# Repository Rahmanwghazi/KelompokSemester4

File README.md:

# Kelompok Mata Kuliah 
Interface, Peripheral, & Komunikasi, Sistem Mikrokontroller dan Sistem Kendali

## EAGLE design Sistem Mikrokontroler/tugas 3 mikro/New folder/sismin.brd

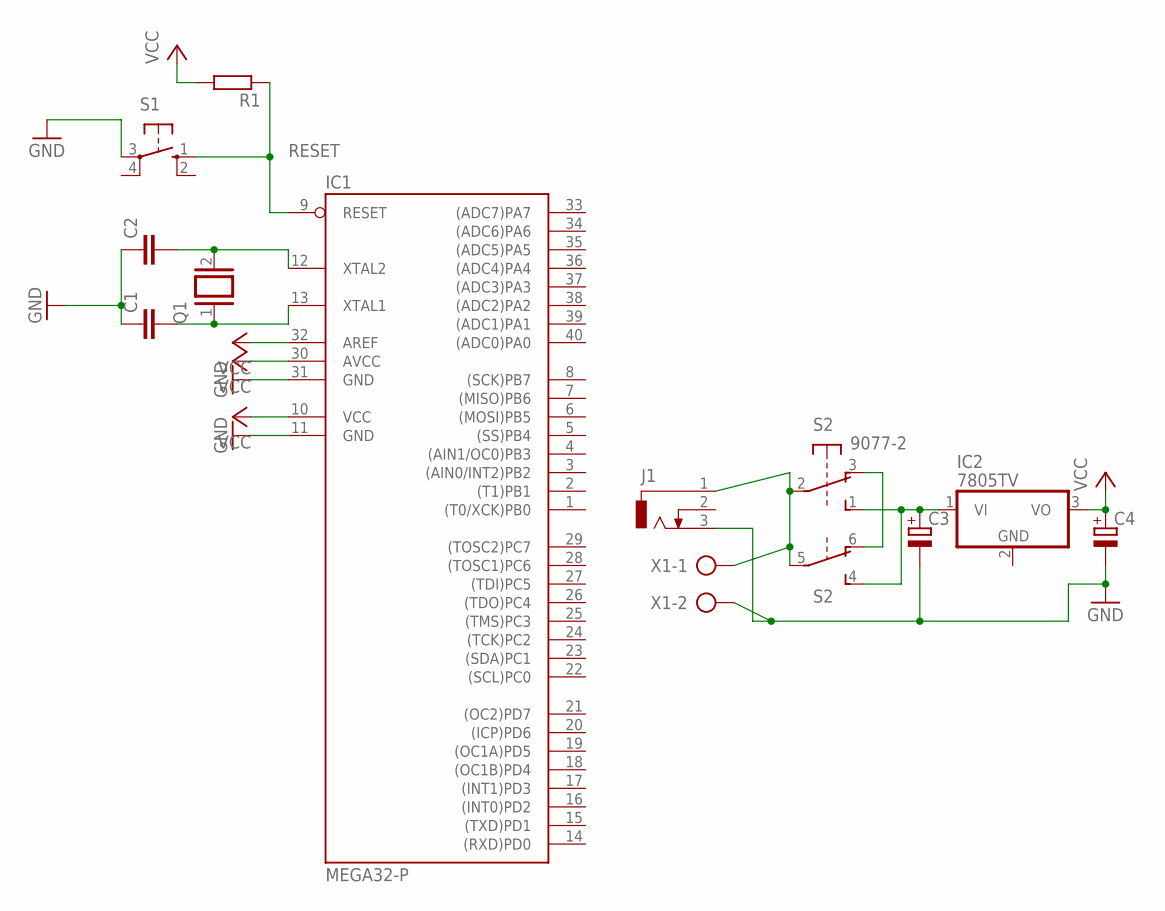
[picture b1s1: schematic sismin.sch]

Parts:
C1, C2: C-EU025-025X050; C025-025X050
C3, C4: CPOL-EUE2.5-5; E2,5-5
IC1: MEGA32-P; DIL40
IC2: 7805TV; TO220V
J1: DCJ0303
Q1: XTAL/S; QS
R1: R-EU_0204/7; 0204/7
S1: 10-XX; B3F-10XX
S2: 9077-2
X1: AK300/2

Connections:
GND: C1.1, C2.1, C3.-, C4.-, IC1.11 (GND), IC1.31 (GND), J1.3, S1.3, X1.2
unnamed: J1.1, S2.2, S2.5, X1.1
unnamed: C2.2, IC1.12 (XTAL2), Q1.2
unnamed: C1.2, IC1.13 (XTAL1), Q1.1
unnamed: S2.3 (O), S2.6 (O)
unnamed: C3.+, IC2.1 (VI), S2.1 (S), S2.4 (S)
RESET: IC1.9 (RESET), R1.1, S1.1 (S)
VCC: C4.+, IC1.10 (VCC), IC1.30 (AVCC), IC1.32 (AREF), IC2.3 (VO), R1.2

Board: 2 copper layers, 12 parts (0 on the bottom side), 8 nets, no tracks yet.

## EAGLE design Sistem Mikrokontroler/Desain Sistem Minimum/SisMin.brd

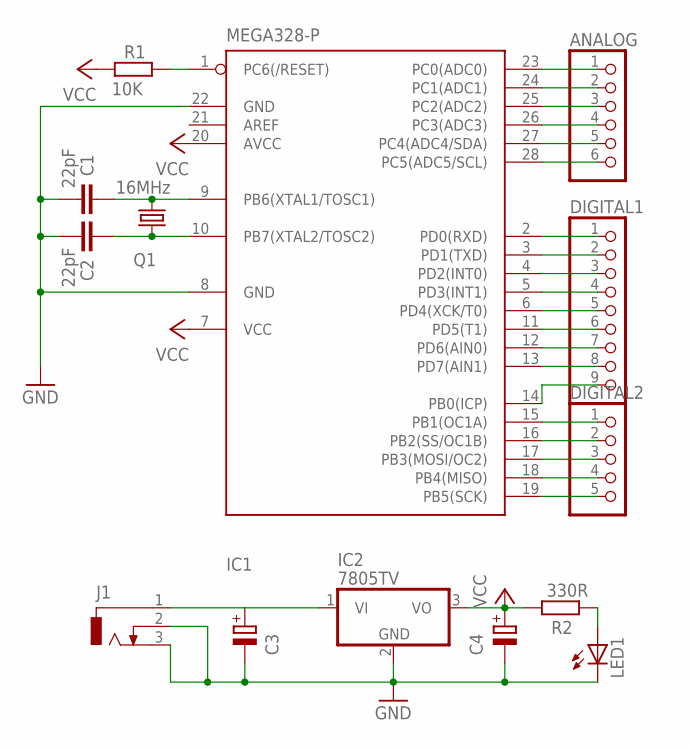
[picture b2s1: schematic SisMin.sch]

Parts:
ANALOG: PINHD-1X6; 1X06
C1, C2: 22pF; C025-024X044
C3, C4: CPOL-EUE2.5-6; E2,5-6
DIGITAL1: PINHD-1X9; 1X09
DIGITAL2: PINHD-1X5; 1X05
IC1: MEGA328-P; DIL28-3
IC2: 7805TV; TO220V
J1: DCJ0303
LED1: LED3MM
Q1: 16MHz; HC49U70
R1: 10K; 0207/10
R2: 330R; 0207/10

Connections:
GND: C1.2, C2.2, C3.-, C4.-, IC1.8 (GND), IC1.22 (GND), IC2.2 (GND), J1.2, J1.3, LED1.K (C)
unnamed: IC1.1 (PC6(/RESET)), R1.2
unnamed: C1.1, IC1.9 (PB6(XTAL1/TOSC1)), Q1.1
unnamed: C2.1, IC1.10 (PB7(XTAL2/TOSC2)), Q1.2
unnamed: ANALOG.1, IC1.23 (PC0(ADC0))
unnamed: ANALOG.2, IC1.24 (PC1(ADC1))
unnamed: ANALOG.3, IC1.25 (PC2(ADC2))
unnamed: ANALOG.4, IC1.26 (PC3(ADC3))
unnamed: ANALOG.5, IC1.27 (PC4(ADC4/SDA))
unnamed: ANALOG.6, IC1.28 (PC5(ADC5/SCL))
unnamed: DIGITAL1.1, IC1.2 (PD0(RXD))
unnamed: DIGITAL1.2, IC1.3 (PD1(TXD))
unnamed: DIGITAL1.3, IC1.4 (PD2(INT0))
unnamed: DIGITAL1.4, IC1.5 (PD3(INT1))
unnamed: DIGITAL1.5, IC1.6 (PD4(XCK/T0))
unnamed: DIGITAL1.6, IC1.11 (PD5(T1))
unnamed: DIGITAL1.7, IC1.12 (PD6(AIN0))
unnamed: DIGITAL1.8, IC1.13 (PD7(AIN1))
unnamed: DIGITAL1.9, IC1.14 (PB0(ICP))
unnamed: DIGITAL2.1, IC1.15 (PB1(OC1A))
unnamed: DIGITAL2.2, IC1.16 (PB2(SS/OC1B))
unnamed: DIGITAL2.3, IC1.17 (PB3(MOSI/OC2))
unnamed: DIGITAL2.4, IC1.18 (PB4(MISO))
unnamed: DIGITAL2.5, IC1.19 (PB5(SCK))
unnamed: C3.+, IC2.1 (VI), J1.1
unnamed: LED1.A, R2.2
VCC: C4.+, IC1.7 (VCC), IC1.20 (AVCC), IC2.3 (VO), R1.1, R2.1

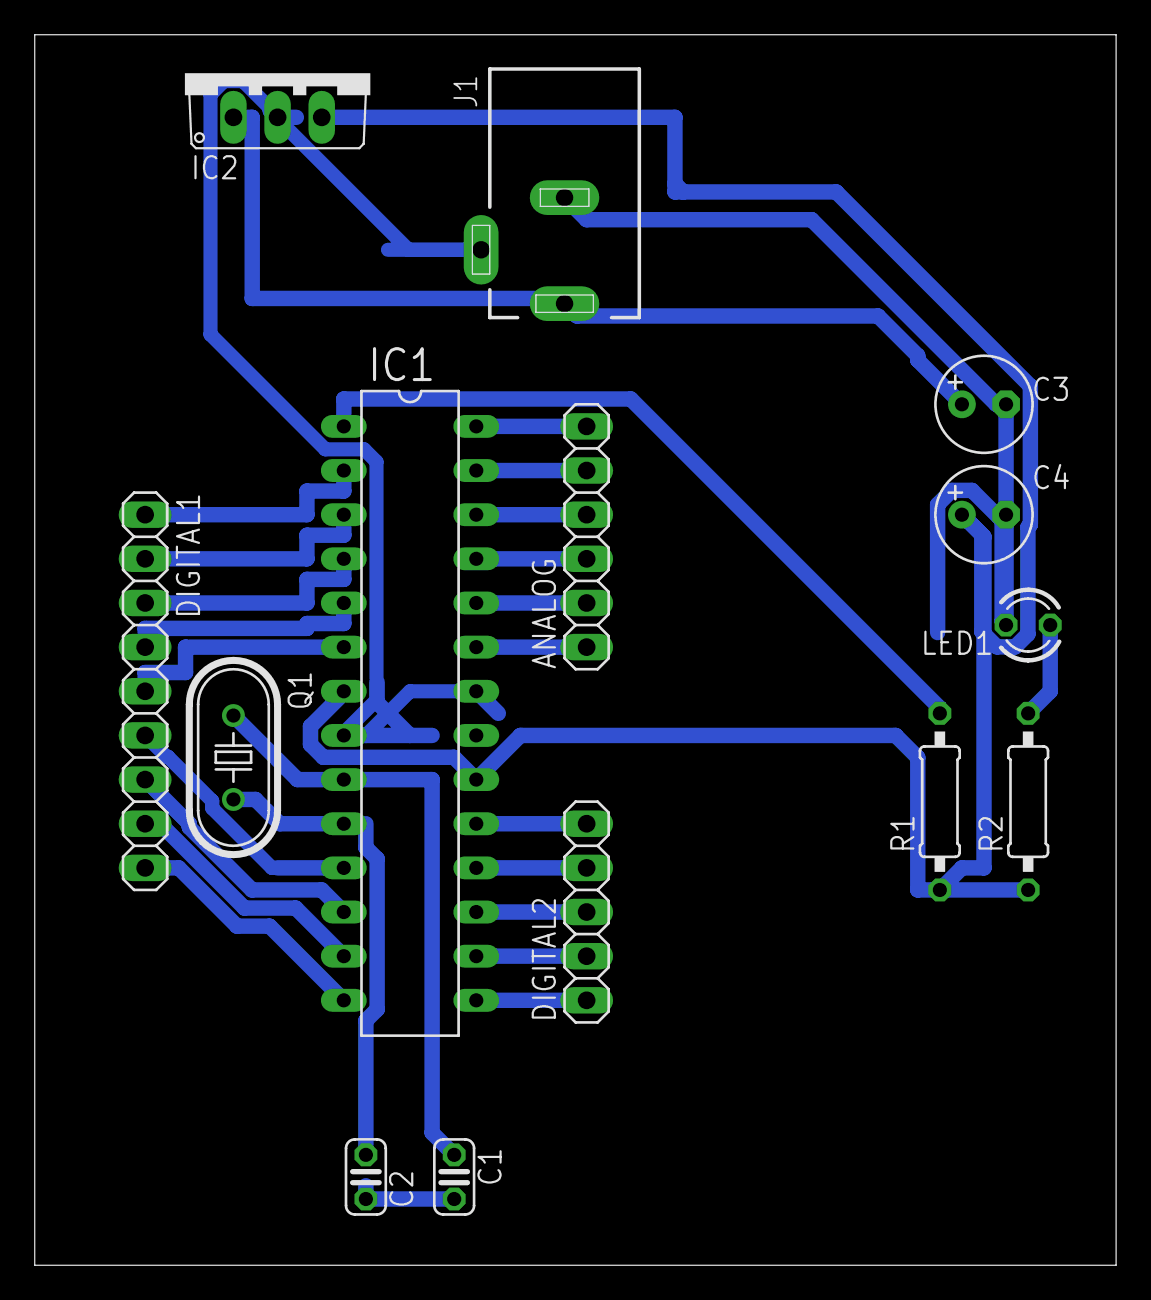
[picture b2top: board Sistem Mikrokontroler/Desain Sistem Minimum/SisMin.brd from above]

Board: 2 copper layers, 62.2 x 70.8 mm, 14 parts (0 on the bottom side), 27 nets.

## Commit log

2021-03-04 tambah tugas 1 sk
2021-03-04 upload ulang
2021-03-04 upload ulang 2
2021-03-05 apdatte gan
2021-03-05 updatte laaagiii
2021-03-07 tugas keypad bagian A
2021-03-07 update yang kasus percobaan
2021-03-07 sistem kendali yang pwm
2021-03-07 perbaiki path file
2021-03-07 update gaaan
2021-03-07 update fiqq
2021-03-09 updateee mikro tugas 3
2021-03-09 update tugas mikro 3
2021-03-09 update tugas kasus percobaan
2021-03-09 perbaiki path
2021-03-09 update praktikum interface 3
2021-03-09 update upload tugas interface 3
2021-03-09 upload sisken
2021-03-09 upload tugas Sistem kendali 3 part 2
2021-03-15 bikin folder modul 4
2021-03-15 upload rangkaiann proteus modul 4 interface
2021-03-15 upload rangkaiann proteus modul 5 interface
2021-03-15 lanjutin kasus eeprom
2021-03-15 update kasus dot matrix
2021-03-16 upload pdf modul 4 interface
2021-03-16 sisken PID P
2021-03-17 laporan sisken PDI P
2021-03-18 modul 5 update
2021-03-19 modul 5 mikro
2021-03-22 update nama file modul 4
2021-03-22 update rangkaian 1 interface
2021-03-22 upload tugas 6 mikro baru LCD
2021-03-25 modul 6
2021-03-25 kasus percobaan modul 5
2021-03-25 assessment wafiq
2021-03-25 upload assessment 1 interface
2021-03-25 update posisi penyimpanan file assessment 1 istmy fathan
2021-03-25 update ulangg
2021-03-25 update file interface 5-6
2021-03-25 update ulang
2021-03-25 upload rangkaian lcd tugass 6 mikro
2021-03-29 upload modul 5-6
2021-03-29 upload assessment 1 sisken
2021-03-30 update assessment
2021-04-05 P dan D
2021-04-14 upload tugas praktikum mandiri
2021-04-14 praktikum mandiri PID wafiq
2021-04-14 rapihin file
2021-04-16 modul 12
2021-04-17 upload laporan PDF
2021-04-23 upload assessmnent 2
2021-04-29 Praktikum mandiri Wafiq
2021-04-29 Praktikum mandiri Wafiq 2
2021-05-02 buat folder
2021-05-02 folder 8
2021-05-02 update link tinkercad
2021-05-02 proximity
2021-05-03 upload rangkaian sama kodingan mod 11
2021-05-03 upload assessment 2 istmy fathan
2021-05-03 rapihin
2021-05-03 upload tugas modul 13 dan 14 interface
2021-05-04 lanjutan implementasi modul 6
2021-05-05 PD EEPROM
2021-05-05 tambah eeprom dan tombol
2021-05-06 PID done
2021-05-21 upload tugas mikro 7
2021-05-21 upload laporan modul 5
2021-05-21 upload laporan modul 6
2021-05-21 rangkaian PIR
2021-05-21 upload rangkaian modul 7
2021-05-21 revisi rangkaian PIR
2021-05-21 modul 7 + code
2021-05-21 bagian B
2021-05-22 modul proximity
2021-05-22 modul 11 bluetooth
2021-05-22 modul 9 proximity
2021-05-24 perbaiki rangkaian modul 13 + modul
2021-05-24 perbaiki rangkaian modul 7 + code bagian 1-2
2021-05-24 perbaiki rangkaian modul 7 + code 1-3
2021-05-24 perbaiki rangkaian modul 7 + code 4
2021-05-26 mikro 7 bagian 7.5
2021-05-26 fuzzy logic 1
2021-05-26 laporan PD
2021-05-30 upload laporan 7 PIR sama link youtube
2021-05-30 upload laporan modul 8 interface
2021-05-31 upload matakuliah interface laporan modul 11
2021-05-31 upload modul 13 matakuliah interface
2021-06-01 upload laporan dan link modul 10 matakuliah interface
2021-06-01 upload kodingan buat motor servo modul 10 interface
2021-06-01 upload ulang laporan modul 10 matakuliah interface
2021-06-05 proposal tubes
2021-06-19 proposal gemastik, modul 5
2021-06-19 modul 7
2021-06-19 uplod laporan modul 6
2021-06-19 upload ulang laporan modul 6
2021-06-19 modul 9 interface
2021-06-20 modul 7 mikro
